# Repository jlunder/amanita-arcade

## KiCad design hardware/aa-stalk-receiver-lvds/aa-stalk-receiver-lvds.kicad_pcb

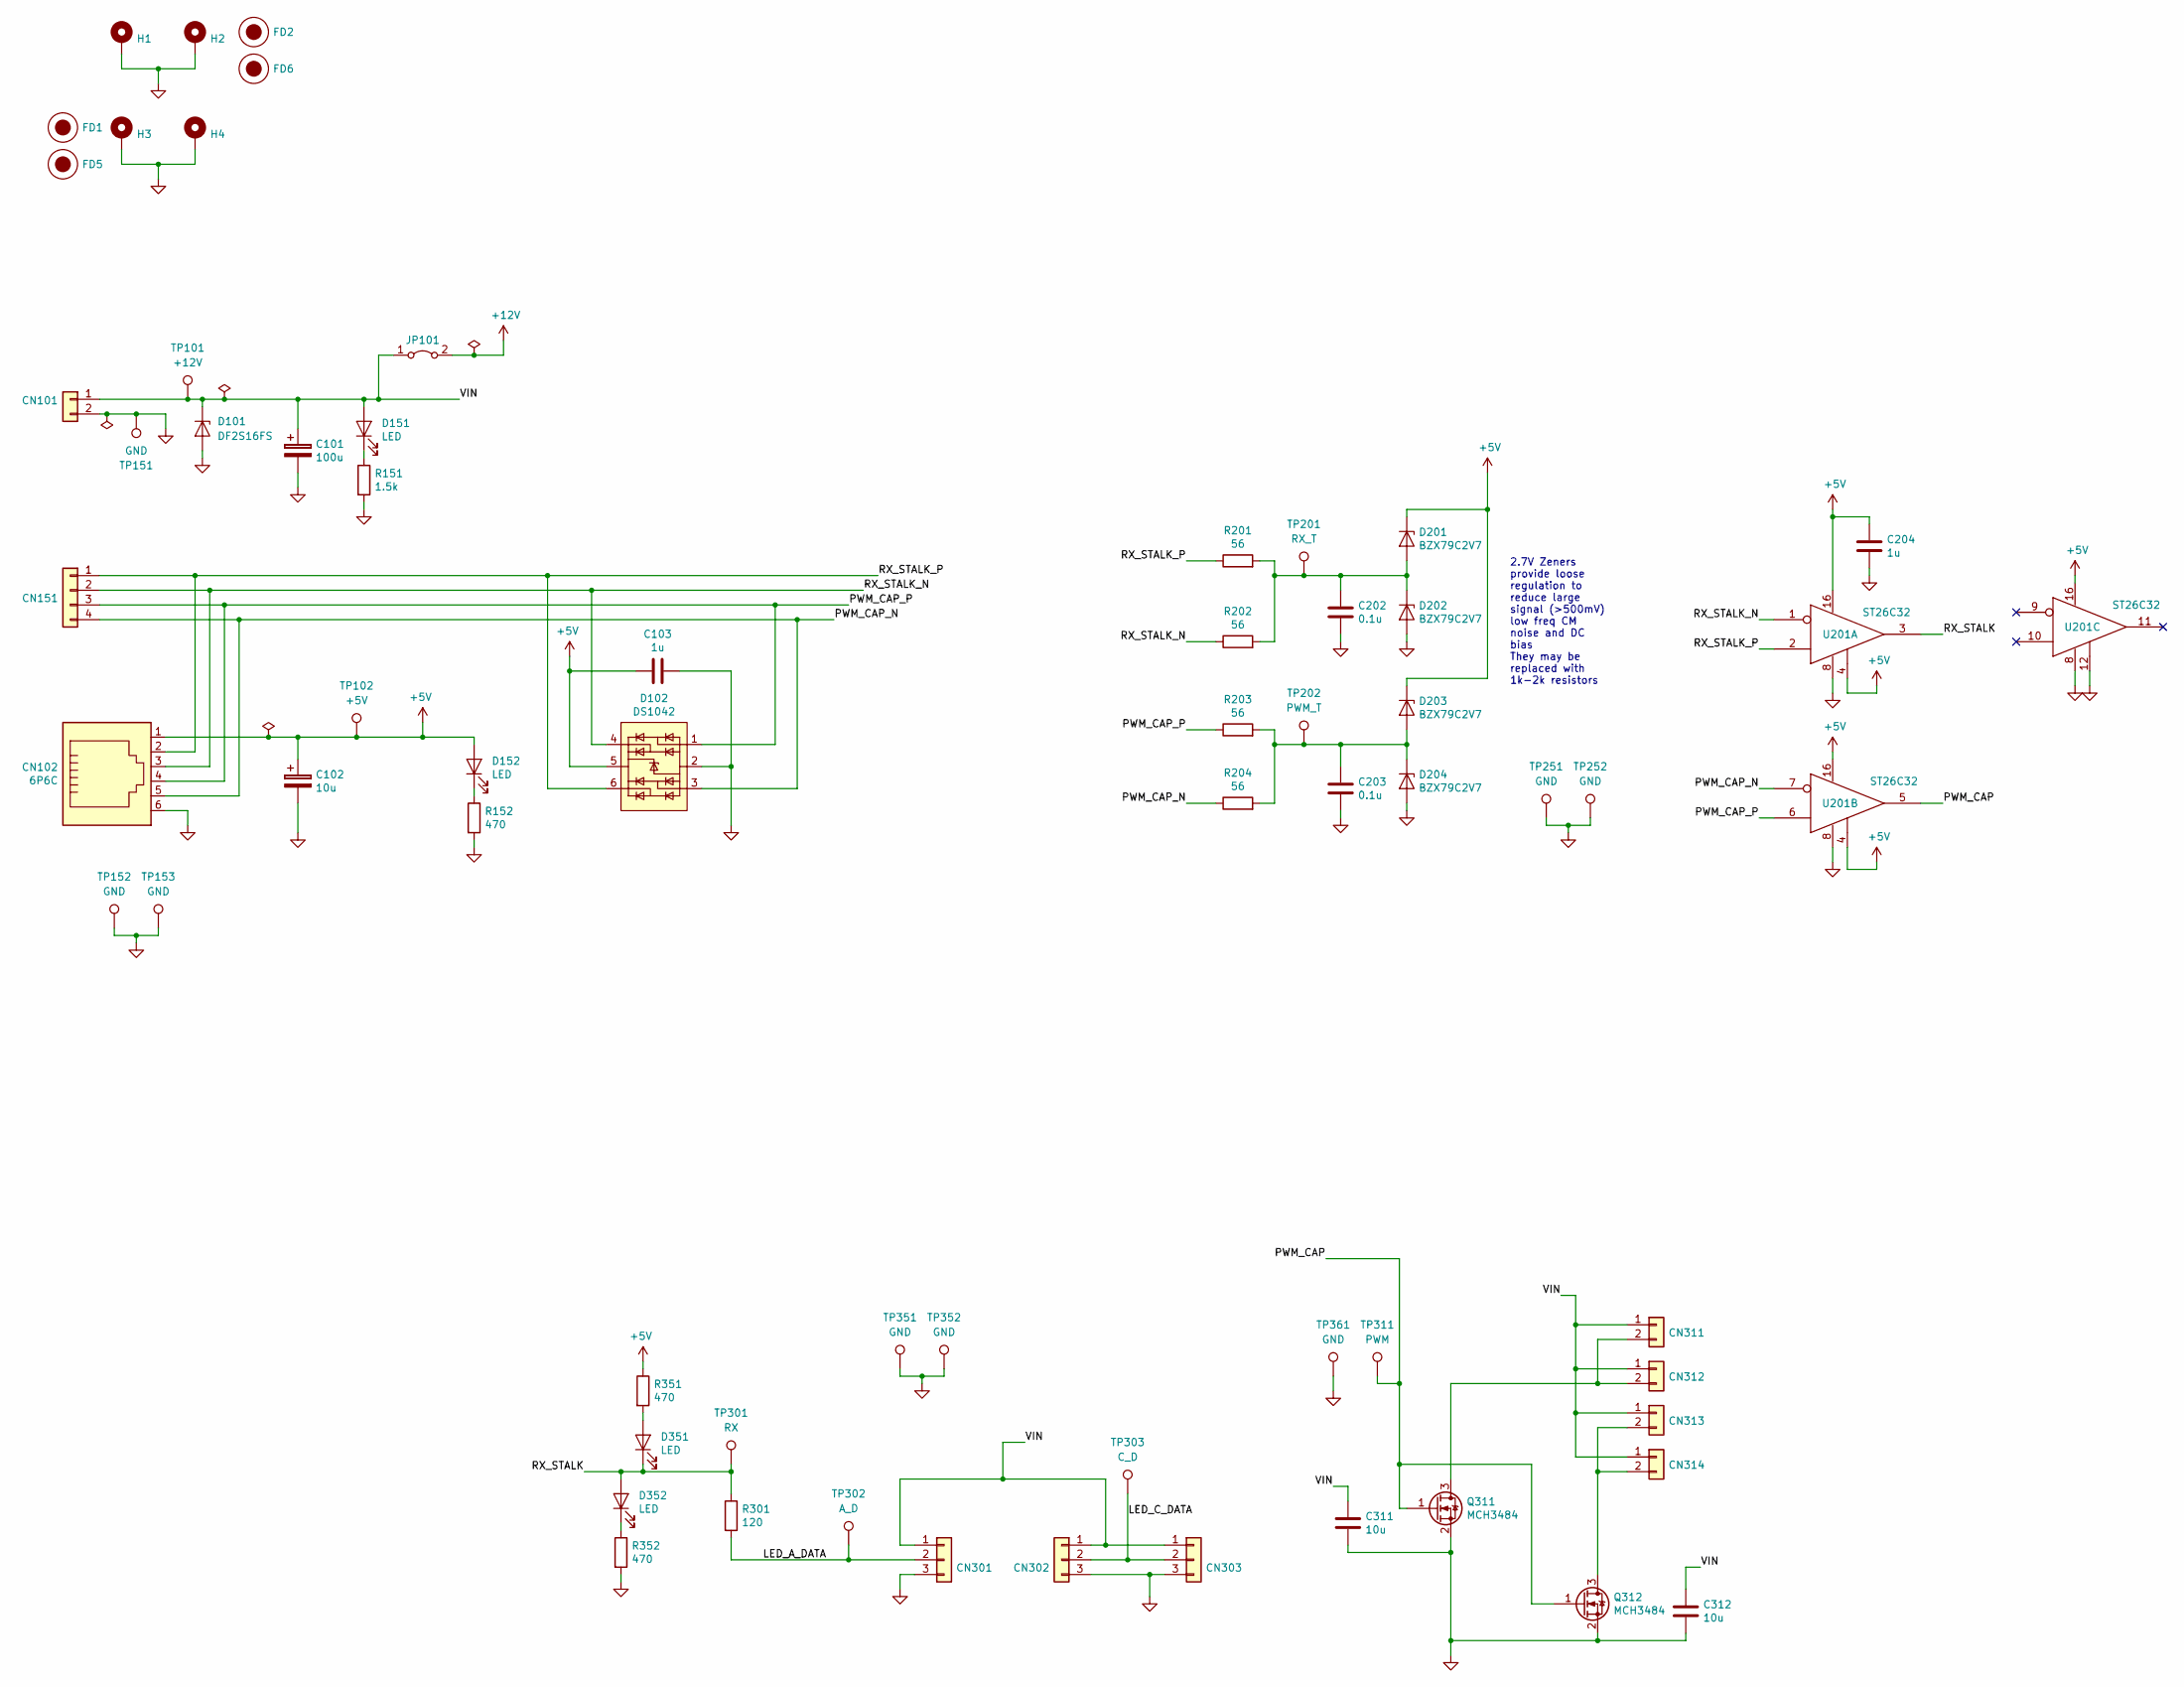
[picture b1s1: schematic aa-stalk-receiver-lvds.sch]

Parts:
C101: 100u; CP_Radial_D10.0mm_P2.50mm_P5.00mm
C102: 10u; CP_Radial_D5.0mm_P2.50mm
C103, C204: 1u; C_0805_2012Metric
C202, C203: 0.1u; C_0805_2012Metric
C311, C312: 10u; C_0805_2012Metric
CN101: Conn_01x02; SolderWirePad_1x02_P7.62mm_Drill2.5mm
CN102: 6P6C; 6P6C_Assmann_A-2014-1-4
CN151: Conn_01x04; PinHeader_1x04_P2.54mm_Vertical
CN301, CN302, CN303: Conn_01x03; PinHeader_1x03_P2.54mm_Vertical
CN311, CN312, CN313, CN314: Conn_01x02; PinHeader_1x02_P2.54mm_Vertical
D101: DF2S16FS; D_SOD-923
D102: DS1042; SOT-23-6
D151, D152, D351, D352: LED; D_0603_1608Metric
D201, D202, D203, D204: BZX79C2V7; D_DO-35_SOD27_P7.62mm_Horizontal
FD1, FD2: Fiducial; Fiducial_1mm_Dia_2.54mm_Outer_CopperTop
FD5, FD6: Fiducial; StencilAlignment_1.27mm
H1, H2, H3, H4: MountingHole_Pad; MountingHole_2.7mm_M2.5_Pad_Via
JP101: Jumper_2_Bridged; PinHeader_1x02_P2.54mm_Vertical
Q311, Q312: MCH3484; SOT-323_SC-70
R151: 1.5k; R_0603_1608Metric
R152, R351, R352: 470; R_0603_1608Metric
R201, R202, R203, R204: 56; R_0603_1608Metric
R301: 120; R_0603_1608Metric
TP101: +12V; TestPoint_Loop_D1.80mm_Drill1.0mm_Beaded
TP102: +5V; TestPoint_Loop_D1.80mm_Drill1.0mm_Beaded
TP151, TP152, TP153, TP251, TP252, TP351, TP352, TP361: GND; TestPoint_Loop_D1.80mm_Drill1.0mm_Beaded
TP201: RX_T; TestPoint_Loop_D1.80mm_Drill1.0mm_Beaded
TP202: PWM_T; TestPoint_Loop_D1.80mm_Drill1.0mm_Beaded
TP301: RX; TestPoint_Loop_D1.80mm_Drill1.0mm_Beaded
TP302: A_D; TestPoint_Loop_D1.80mm_Drill1.0mm_Beaded
TP303: C_D; TestPoint_Loop_D1.80mm_Drill1.0mm_Beaded
TP311: PWM; TestPoint_Loop_D1.80mm_Drill1.0mm_Beaded
U201: ST26C32; SOIC-16_3.9x9.9mm_P1.27mm

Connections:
+5V: C102.1, C103.2, C204.1, CN102.1, D102.5 (K), D152.2 (A), D201.1 (K), D203.1 (K), R351.1, TP102.1, U201.4 (ENABLE), U201.16 (VCC)
+12V: JP101.2 (B)
/LED_A_DATA: CN301.2, R301.2, TP302.1
/LED_C_DATA: CN302.2, CN303.2, TP303.1
/PWM_CAP: Q311.1 (G), Q312.1 (G), TP311.1, U201.5 (OUT)
/PWM_CAP_N: CN102.5, CN151.4, D102.3 (K), R204.1, U201.7 (E-)
/PWM_CAP_P: CN102.4, CN151.3, D102.1 (K), R203.1, U201.6 (E+)
/RX_STALK: D351.1 (K), D352.2 (A), R301.1, TP301.1, U201.3 (OUT)
/RX_STALK_N: CN102.3, CN151.2, D102.4 (K), R202.1, U201.1 (E-)
/RX_STALK_P: CN102.2, CN151.1, D102.6 (K), R201.1, U201.2 (E+)
/VIN: C101.1, C311.1, C312.1, CN101.1, CN301.1, CN302.1, CN303.1, CN311.1, CN312.1, CN313.1, CN314.1, D101.1 (K), D151.2 (A), JP101.1 (A), TP101.1
GND: C101.2, C102.2, C103.1, C202.2, C203.2, C204.2, C311.2, C312.2, CN101.2, CN102.6, CN301.3, CN302.3, CN303.3, D101.2 (A), D102.2 (A), D202.2 (A), D204.2 (A), H1.1, H2.1, H3.1, H4.1, Q311.2 (S), Q312.2 (S), R151.2, R152.2, R352.2, TP151.1, TP152.1, TP153.1, TP251.1, TP252.1, TP351.1, TP352.1, TP361.1, U201.8 (GND), U201.12 (ENABLE)
unnamed: C202.1, D201.2 (A), D202.1 (K), R201.2, R202.2, TP201.1
unnamed: C203.1, D203.2 (A), D204.1 (K), R203.2, R204.2, TP202.1
unnamed: CN311.2, CN312.2, Q311.3 (D)
unnamed: CN313.2, CN314.2, Q312.3 (D)
unnamed: D151.1 (K), R151.1
unnamed: D152.1 (K), R152.1
unnamed: D351.2 (A), R351.2
unnamed: D352.1 (K), R352.1

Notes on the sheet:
2.7V Zeners provide loose regulation to reduce large signal (>500mV) low freq CM noise and DC bias They may be replaced with 1k-2k resistors

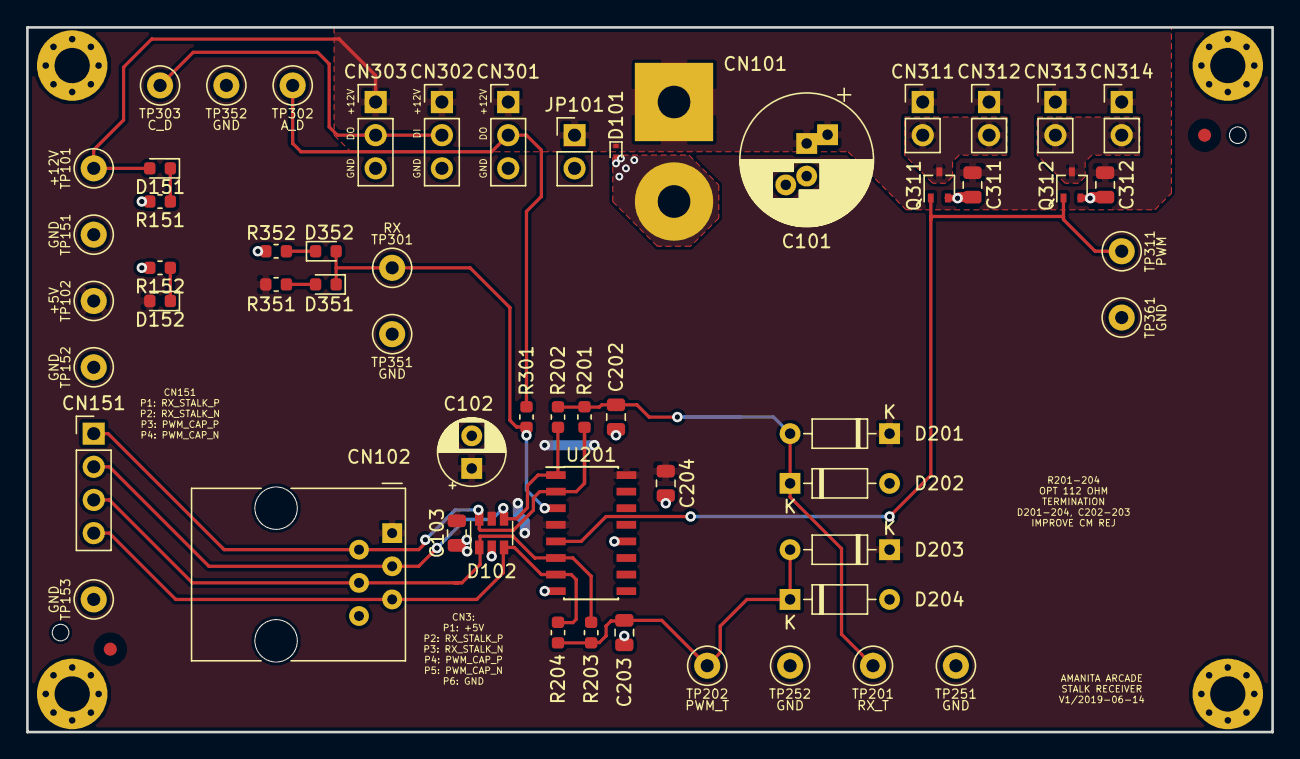
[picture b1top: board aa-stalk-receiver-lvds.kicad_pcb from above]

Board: 2 copper layers, 95.4 x 54.0 mm, 65 parts (0 on the bottom side), 19 nets.

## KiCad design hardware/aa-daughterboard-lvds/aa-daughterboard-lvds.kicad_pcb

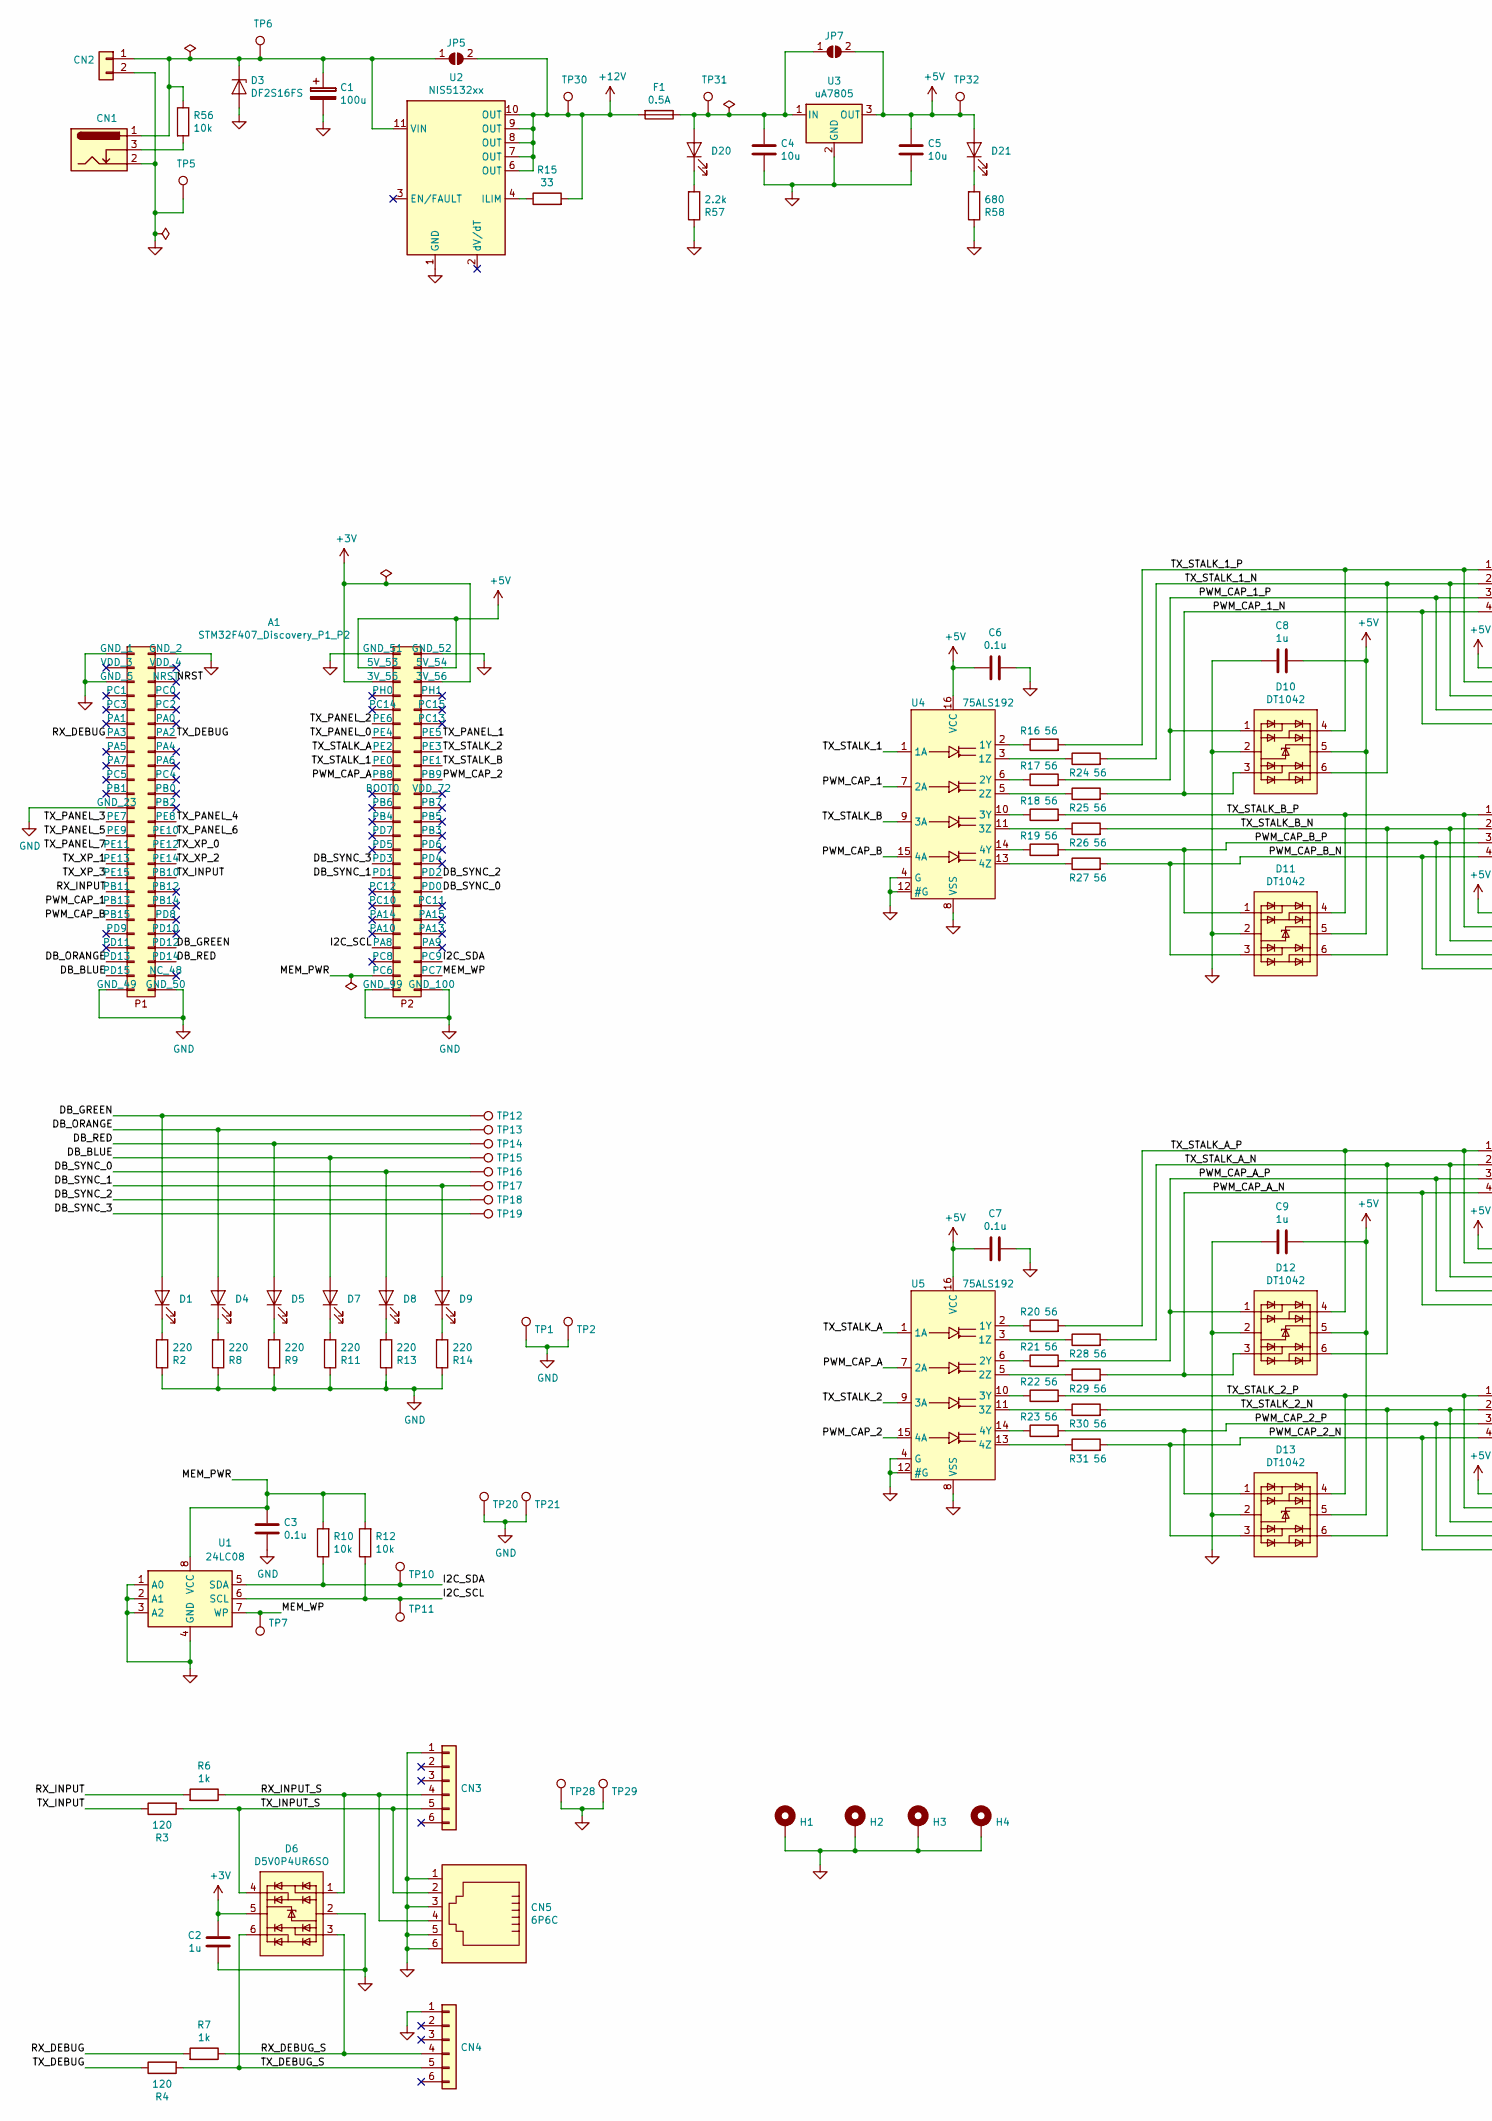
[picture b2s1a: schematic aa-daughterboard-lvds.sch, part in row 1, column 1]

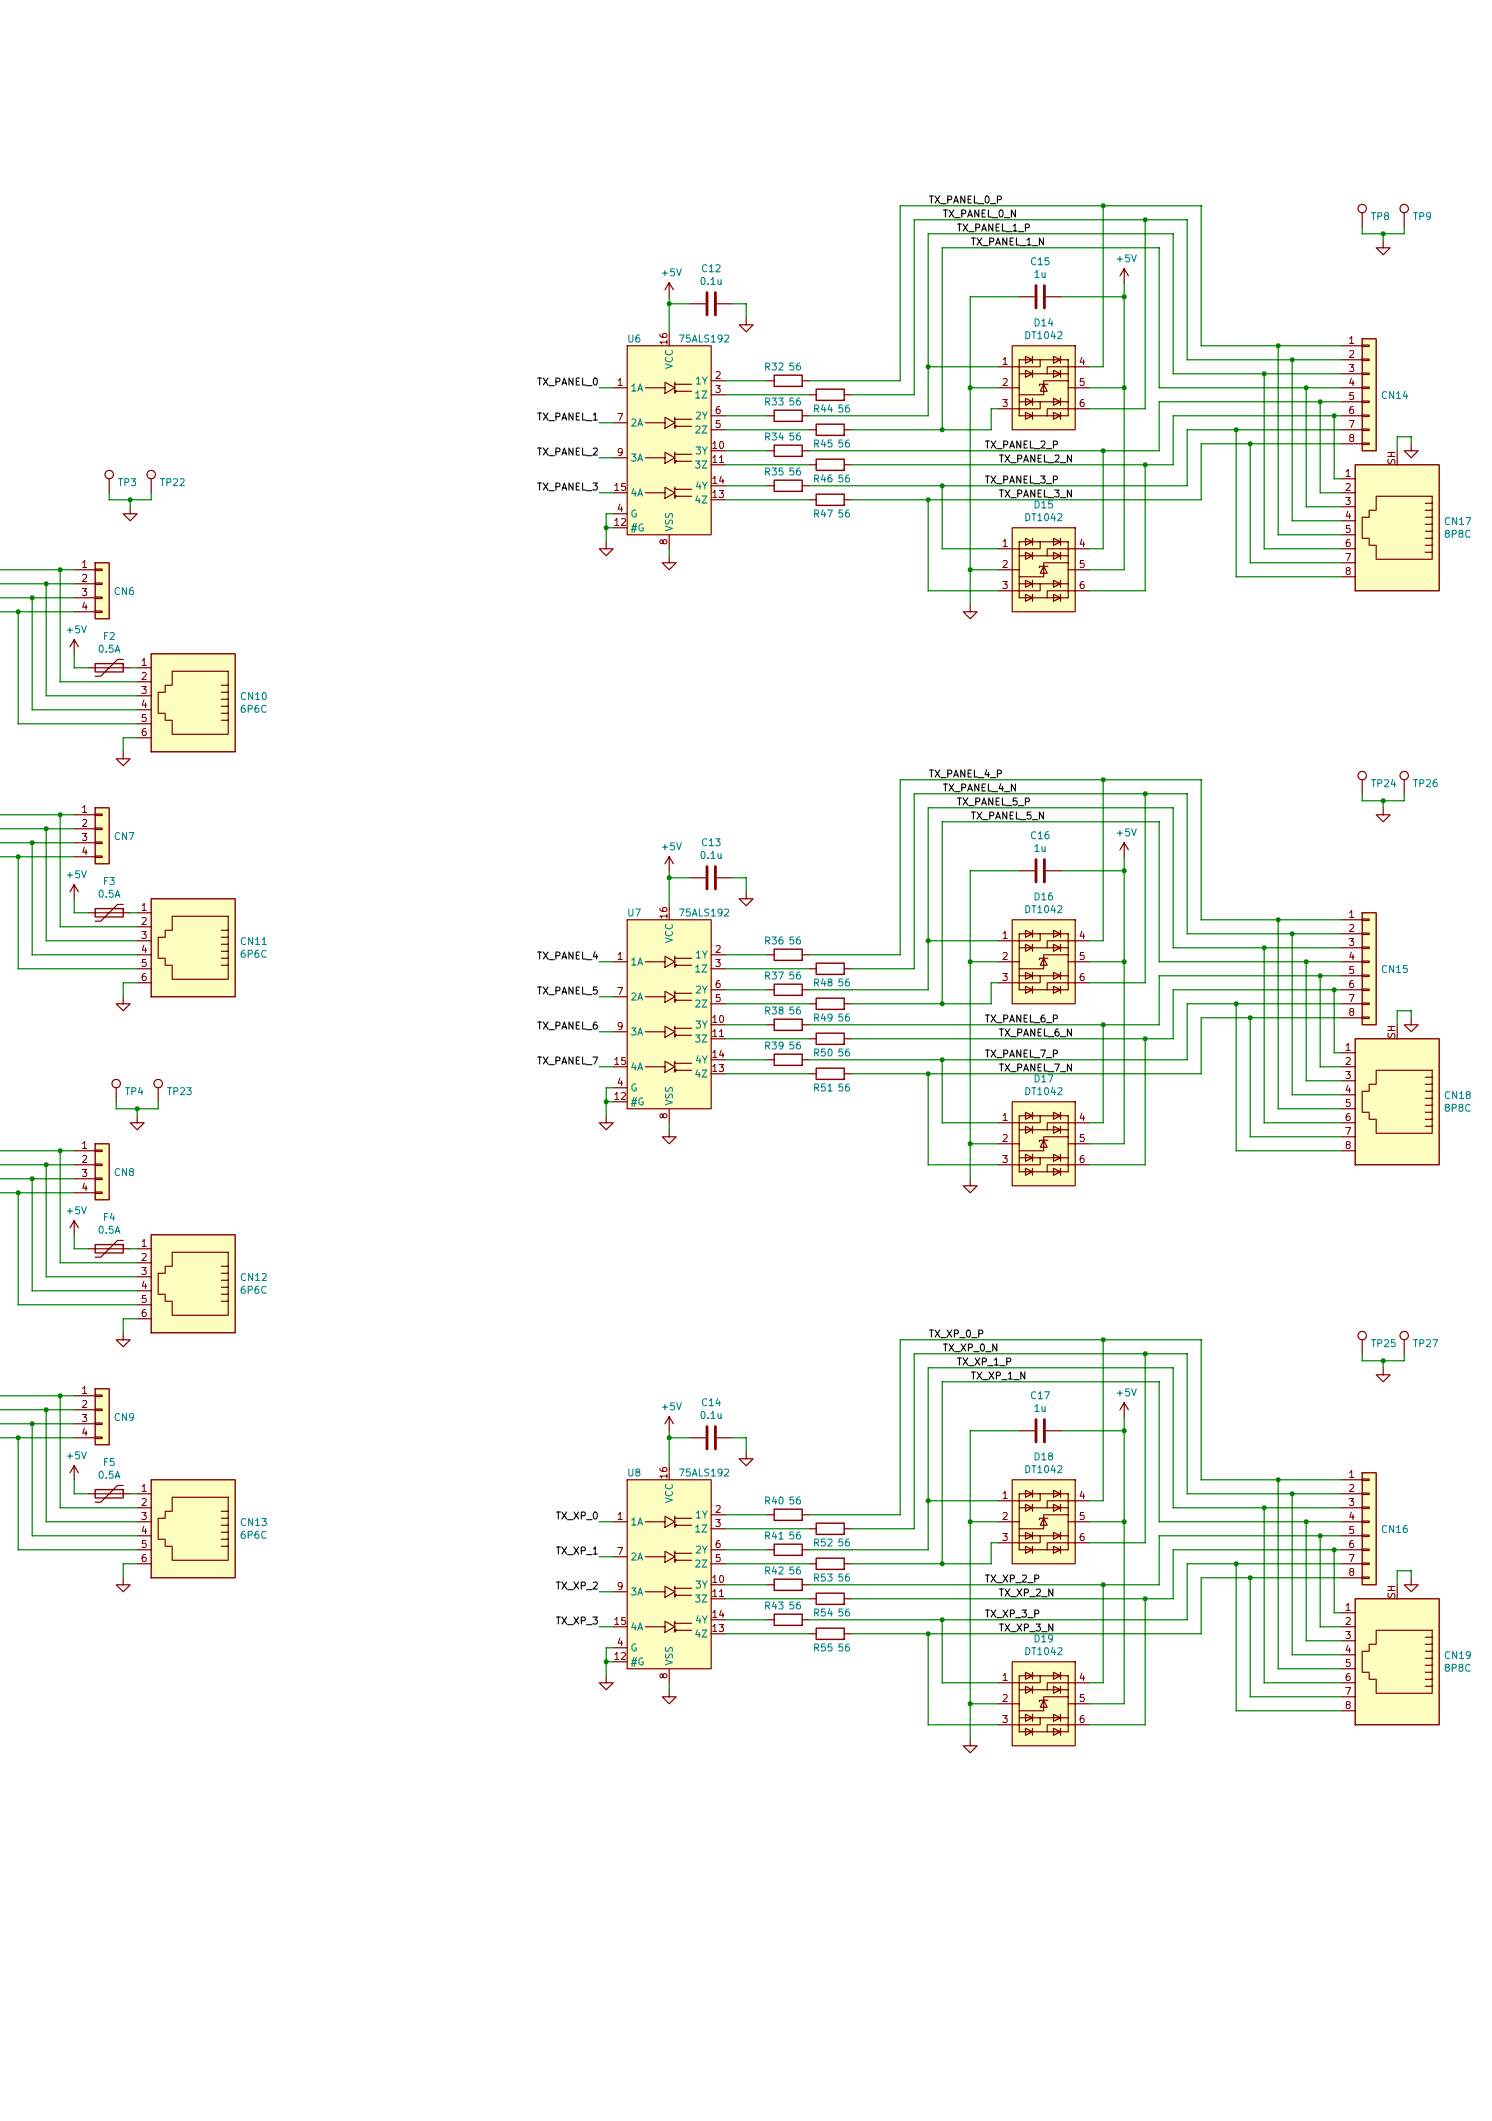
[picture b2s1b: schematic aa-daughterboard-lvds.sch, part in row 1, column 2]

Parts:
A1: STM32F407_Discovery_P1_P2; STM32F407_Discovery_P1_P2_Socket
C1: 100u; CP_Radial_D10.0mm_P2.50mm_P5.00mm
C2, C8, C9, C15, C16, C17: 1u; C_0805_2012Metric
C3, C6, C7, C12, C13, C14: 0.1u; C_0603_1608Metric
C4, C5: 10u; C_0805_2012Metric
CN1: Barrel_Jack; BarrelJack_Horizontal
CN2: Conn_01x02; SolderWirePad_1x02_P5.08mm_Drill1.5mm
CN3, CN4: Conn_01x06; PinHeader_1x06_P2.54mm_Vertical
CN5, CN10, CN11, CN12, CN13: 6P6C; 6P6C_Assmann_A-2014-1-4
CN6, CN7, CN8, CN9: Conn_01x04; PinHeader_1x04_P2.54mm_Vertical
CN14, CN15, CN16: Conn_01x08; PinHeader_2x04_P2.54mm_Vertical
CN17, CN18, CN19: 8P8C; 8P8C_Assmann_A-2014-2S-4
D1, D4, D5, D7, D8, D9, D20, D21: LED; LED_0603_1608Metric
D3: DF2S16FS; D_SOD-923
D6: D5V0P4UR6SO; SOT-23-6
D10, D11, D12, D13, D14, D15, D16, D17, D18, D19: DT1042; SOT-23-6
F1: 0.5A; Fuseholder_Clip_5x20_Bel_FC-211-22
F2, F3, F4, F5: 0.5A; Fuse_0805_2012Metric
H1, H2, H3, H4: MountingHole_Pad; MountingHole_4.3mm_M4_Pad_Via
JP5, JP7: SolderJumper_2_Open; SolderJumper-2_P1.3mm_Open_RoundedPad1.0x1.5mm
R2, R8, R9, R11, R13, R14: 220; R_0603_1608Metric
R3, R4: 120; R_0603_1608Metric
R6, R7: 1k; R_0603_1608Metric
R10, R12, R56: 10k; R_0603_1608Metric
R15: 33; R_0603_1608Metric
R16, R17, R18, R19, R20, R21, R22, R23, R24, R25, R26, R27, R28, R29, R30, R31, R32, R33, R34, R35, R36, R37, R38, R39, R40, R41, R42, R43, R44, R45, R46, R47, R48, R49, R50, R51, R52, R53, R54, R55: 56; R_0603_1608Metric
R57: 2.2k; R_0603_1608Metric
R58: 680; R_0603_1608Metric
TP1, TP2, TP3, TP4, TP5, TP6, TP7, TP8, TP9, TP10, TP11, TP12, TP13, TP14, TP15, TP16, TP17, TP18, TP19, TP20, TP21, TP22, TP23, TP24, TP25, TP26, TP27, TP28, TP29, TP30, TP31, TP32: TestPoint; TestPoint_THTPad_D2.0mm_Drill1.0mm
U1: 24LC08; DIP-8_W7.62mm_Socket
U2: NIS5132xx; DFN-10-1EP_3x3mm_P0.5mm_EP1.75x2.7mm
U3: uA7805; TO-220-3_Horizontal_TabDown
U4, U5, U6, U7, U8: 75ALS192; SOIC-16_3.9x9.9mm_P1.27mm

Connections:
+3V: A1.P2_5 (3V_55), A1.P2_6 (3V_56), C2.1, D6.5 (K)
+5V: A1.P2_3 (5V_53), A1.P2_4 (5V_54), C5.1, C6.1, C7.1, C8.2, C9.2, C12.1, C13.1, C14.1, C15.2, C16.2, C17.2, D10.5 (K), D11.5 (K), D12.5 (K), D13.5 (K), D14.5 (K), D15.5 (K), D16.5 (K), D17.5 (K), D18.5 (K), D19.5 (K), D21.2 (A), F2.2, F3.2, F4.2, F5.2, JP7.2 (B), TP32.1, U3.3 (OUT), U4.16 (VCC), U5.16 (VCC), U6.16 (VCC), U7.16 (VCC), U8.16 (VCC); also elsewhere on the board
+12V: F1.2, JP5.2 (B), R15.2, TP30.1, U2.6 (OUT), U2.7 (OUT), U2.8 (OUT), U2.9 (OUT), U2.10 (OUT)
/DB_BLUE: A1.P1_47 (PD15), D7.2 (A), TP15.1
/DB_GREEN: A1.P1_44 (PD12), D1.2 (A), TP12.1
/DB_ORANGE: A1.P1_45 (PD13), D4.2 (A), TP13.1
/DB_RED: A1.P1_46 (PD14), D5.2 (A), TP14.1
/DB_SYNC_0: A1.P2_36 (PD0), D8.2 (A), TP16.1
/DB_SYNC_1: A1.P2_33 (PD1), D9.2 (A), TP17.1
/DB_SYNC_2: A1.P2_34 (PD2), TP18.1
/DB_SYNC_3: A1.P2_31 (PD3), TP19.1
/I2C_SCL: A1.P2_43 (PA8), R12.1, TP11.1, U1.6 (SCL)
/I2C_SDA: A1.P2_46 (PC9), R10.1, TP10.1, U1.5 (SDA)
/MEM_PWR: A1.P2_47 (PC6), C3.1, R10.2, R12.2, U1.8 (VCC)
/MEM_WP: A1.P2_48 (PC7), TP7.1, U1.7 (WP)
/NRST: A1.P1_6 (NRST)
/PWM_CAP_1: A1.P1_37 (PB13), U4.7 (2A)
/PWM_CAP_1_N: CN6.4, CN10.5, D10.3 (K), R25.2
/PWM_CAP_1_P: CN6.3, CN10.4, D10.1 (K), R17.2
/PWM_CAP_2: A1.P2_20 (PB9), U5.15 (4A)
/PWM_CAP_2_N: CN9.4, CN13.5, D13.3 (K), R31.2
/PWM_CAP_2_P: CN9.3, CN13.4, D13.1 (K), R23.2
/PWM_CAP_A: A1.P2_19 (PB8), U5.7 (2A)
/PWM_CAP_A_N: CN8.4, CN12.5, D12.3 (K), R29.2
/PWM_CAP_A_P: CN8.3, CN12.4, D12.1 (K), R21.2
/PWM_CAP_B: A1.P1_39 (PB15), U4.15 (4A)
/PWM_CAP_B_N: CN7.4, CN11.5, D11.3 (K), R27.2
/PWM_CAP_B_P: CN7.3, CN11.4, D11.1 (K), R19.2
/RX_DEBUG: A1.P1_13 (PA3), R7.2
/RX_DEBUG_S: CN4.4, D6.3 (K), R7.1
/RX_INPUT: A1.P1_35 (PB11), R6.2
/RX_INPUT_S: CN3.4, CN5.4, D6.1 (K), R6.1
/TX_DEBUG: A1.P1_14 (PA2), R4.1
/TX_DEBUG_S: CN4.5, D6.6 (K), R4.2
/TX_INPUT: A1.P1_34 (PB10), R3.1
/TX_INPUT_S: CN3.5, CN5.2, D6.4 (K), R3.2
/TX_PANEL_0: A1.P2_13 (PE4), U6.1 (1A)
/TX_PANEL_0_N: CN14.2, CN17.4, D14.6 (K), R44.2
/TX_PANEL_0_P: CN14.1, CN17.5, D14.4 (K), R32.2
/TX_PANEL_1: A1.P2_14 (PE5), U6.7 (2A)
/TX_PANEL_1_N: CN14.4, CN17.3, D14.3 (K), R45.2
/TX_PANEL_1_P: CN14.3, CN17.6, D14.1 (K), R33.2
/TX_PANEL_2: A1.P2_11 (PE6), U6.9 (3A)
/TX_PANEL_2_N: CN14.6, CN17.1, D15.6 (K), R46.2
/TX_PANEL_2_P: CN14.5, CN17.2, D15.4 (K), R34.2
/TX_PANEL_3: A1.P1_25 (PE7), U6.15 (4A)
/TX_PANEL_3_N: CN14.8, CN17.7, D15.3 (K), R47.2
/TX_PANEL_3_P: CN14.7, CN17.8, D15.1 (K), R35.2
/TX_PANEL_4: A1.P1_26 (PE8), U7.1 (1A)
/TX_PANEL_4_N: CN15.2, CN18.4, D16.6 (K), R48.2
/TX_PANEL_4_P: CN15.1, CN18.5, D16.4 (K), R36.2
/TX_PANEL_5: A1.P1_27 (PE9), U7.7 (2A)
/TX_PANEL_5_N: CN15.4, CN18.3, D16.3 (K), R49.2
/TX_PANEL_5_P: CN15.3, CN18.6, D16.1 (K), R37.2
/TX_PANEL_6: A1.P1_28 (PE10), U7.9 (3A)
/TX_PANEL_6_N: CN15.6, CN18.1, D17.6 (K), R50.2
/TX_PANEL_6_P: CN15.5, CN18.2, D17.4 (K), R38.2
/TX_PANEL_7: A1.P1_29 (PE11), U7.15 (4A)
/TX_PANEL_7_N: CN15.8, CN18.7, D17.3 (K), R51.2
/TX_PANEL_7_P: CN15.7, CN18.8, D17.1 (K), R39.2
/TX_STALK_1: A1.P2_17 (PE0), U4.1 (1A)
/TX_STALK_1_N: CN6.2, CN10.3, D10.6 (K), R24.2
/TX_STALK_1_P: CN6.1, CN10.2, D10.4 (K), R16.2
/TX_STALK_2: A1.P2_16 (PE3), U5.9 (3A)
/TX_STALK_2_N: CN9.2, CN13.3, D13.6 (K), R30.2
/TX_STALK_2_P: CN9.1, CN13.2, D13.4 (K), R22.2
/TX_STALK_A: A1.P2_15 (PE2), U5.1 (1A)
/TX_STALK_A_N: CN8.2, CN12.3, D12.6 (K), R28.2
/TX_STALK_A_P: CN8.1, CN12.2, D12.4 (K), R20.2
/TX_STALK_B: A1.P2_18 (PE1), U4.9 (3A)
/TX_STALK_B_N: CN7.2, CN11.3, D11.6 (K), R26.2
/TX_STALK_B_P: CN7.1, CN11.2, D11.4 (K), R18.2
/TX_XP_0: A1.P1_30 (PE12), U8.1 (1A)
/TX_XP_0_N: CN16.2, CN19.4, D18.6 (K), R52.2
/TX_XP_0_P: CN16.1, CN19.5, D18.4 (K), R40.2
/TX_XP_1: A1.P1_31 (PE13), U8.7 (2A)
/TX_XP_1_N: CN16.4, CN19.3, D18.3 (K), R53.2
/TX_XP_1_P: CN16.3, CN19.6, D18.1 (K), R41.2
/TX_XP_2: A1.P1_32 (PE14), U8.9 (3A)
/TX_XP_2_N: CN16.6, CN19.1, D19.6 (K), R54.2
/TX_XP_2_P: CN16.5, CN19.2, D19.4 (K), R42.2
/TX_XP_3: A1.P1_33 (PE15), U8.15 (4A)
/TX_XP_3_N: CN16.8, CN19.7, D19.3 (K), R55.2
/TX_XP_3_P: CN16.7, CN19.8, D19.1 (K), R43.2
GND: A1.P1_1 (GND_1), A1.P1_2 (GND_2), A1.P1_5 (GND_5), A1.P1_23 (GND_23), A1.P1_49 (GND_49), A1.P1_50 (GND_50), A1.P2_1 (GND_51), A1.P2_2 (GND_52), A1.P2_49 (GND_99), A1.P2_50 (GND_100), C1.2, C2.2, C3.2, C4.2, C5.2, C6.2, C7.2, C8.1, C9.1, C12.2, C13.2, C14.2, C15.1, C16.1, C17.1, CN1.2, CN2.2, CN3.1, CN4.1, CN5.1, CN5.3, CN5.5, CN5.6, CN10.6, CN11.6, CN12.6, CN13.6, CN17.SH, CN18.SH, CN19.SH, D3.2 (A), D6.2 (A), D10.2 (A), D11.2 (A), D12.2 (A), D13.2 (A), D14.2 (A), D15.2 (A), D16.2 (A), D17.2 (A), D18.2 (A), D19.2 (A), H1.1, H2.1, H3.1, H4.1, R2.1, R8.1, R9.1, R11.1, R13.1, R14.1, R57.1, R58.1, TP1.1, TP2.1, TP3.1, TP4.1, TP5.1, TP8.1, TP9.1, TP20.1, TP21.1, TP22.1, TP23.1, TP24.1, TP25.1, TP26.1, TP27.1, TP28.1, TP29.1, U1.1 (A0), U1.2 (A1), U1.3 (A2), U1.4 (GND), U2.1 (GND), U3.2 (GND), U4.4 (G), U4.8 (VSS), U4.12 (#G), U5.4 (G), U5.8 (VSS), U5.12 (#G), U6.4 (G), U6.8 (VSS), U6.12 (#G), U7.4 (G), U7.8 (VSS), U7.12 (#G), U8.4 (G), U8.8 (VSS), U8.12 (#G); also elsewhere on the board
unnamed: C1.1, CN1.1, CN2.1, D3.1 (K), JP5.1 (A), R56.1, TP6.1, U2.11 (VIN)
unnamed 135: C4.1, D20.2 (A), F1.1, JP7.1 (A), TP31.1, U3.1 (IN); also elsewhere on the board
unnamed: CN1.3, R56.2
unnamed: CN10.1, F2.1
unnamed: CN11.1, F3.1
unnamed: CN12.1, F4.1
unnamed: CN13.1, F5.1
unnamed: D1.1 (K), R2.2
unnamed: D4.1 (K), R8.2
unnamed: D5.1 (K), R9.2
unnamed: D7.1 (K), R11.2
unnamed: D8.1 (K), R13.2
unnamed: D9.1 (K), R14.2
unnamed: D20.1 (K), R57.2
unnamed: D21.1 (K), R58.2
unnamed: R15.1, U2.4 (ILIM)
unnamed: R16.1, U4.2 (1Y)
unnamed: R17.1, U4.6 (2Y)
unnamed: R18.1, U4.10 (3Y)
unnamed: R19.1, U4.14 (4Y)
unnamed: R20.1, U5.2 (1Y)
unnamed: R21.1, U5.6 (2Y)
unnamed: R22.1, U5.10 (3Y)
unnamed: R23.1, U5.14 (4Y)
unnamed: R24.1, U4.3 (1Z)
unnamed: R25.1, U4.5 (2Z)
unnamed: R26.1, U4.11 (3Z)
unnamed: R27.1, U4.13 (4Z)
unnamed: R28.1, U5.3 (1Z)
unnamed: R29.1, U5.5 (2Z)
unnamed: R30.1, U5.11 (3Z)
unnamed: R31.1, U5.13 (4Z)
unnamed: R32.1, U6.2 (1Y)
unnamed: R33.1, U6.6 (2Y)
unnamed: R34.1, U6.10 (3Y)
unnamed: R35.1, U6.14 (4Y)
unnamed: R36.1, U7.2 (1Y)
unnamed: R37.1, U7.6 (2Y)
unnamed: R38.1, U7.10 (3Y)
unnamed: R39.1, U7.14 (4Y)
unnamed: R40.1, U8.2 (1Y)
unnamed: R41.1, U8.6 (2Y)
unnamed: R42.1, U8.10 (3Y)
unnamed: R43.1, U8.14 (4Y)
unnamed: R44.1, U6.3 (1Z)
unnamed: R45.1, U6.5 (2Z)
unnamed: R46.1, U6.11 (3Z)
unnamed: R47.1, U6.13 (4Z)
unnamed: R48.1, U7.3 (1Z)
unnamed: R49.1, U7.5 (2Z)
unnamed: R50.1, U7.11 (3Z)
unnamed: R51.1, U7.13 (4Z)
unnamed: R52.1, U8.3 (1Z)
unnamed: R53.1, U8.5 (2Z)
unnamed: R54.1, U8.11 (3Z)
unnamed: R55.1, U8.13 (4Z)

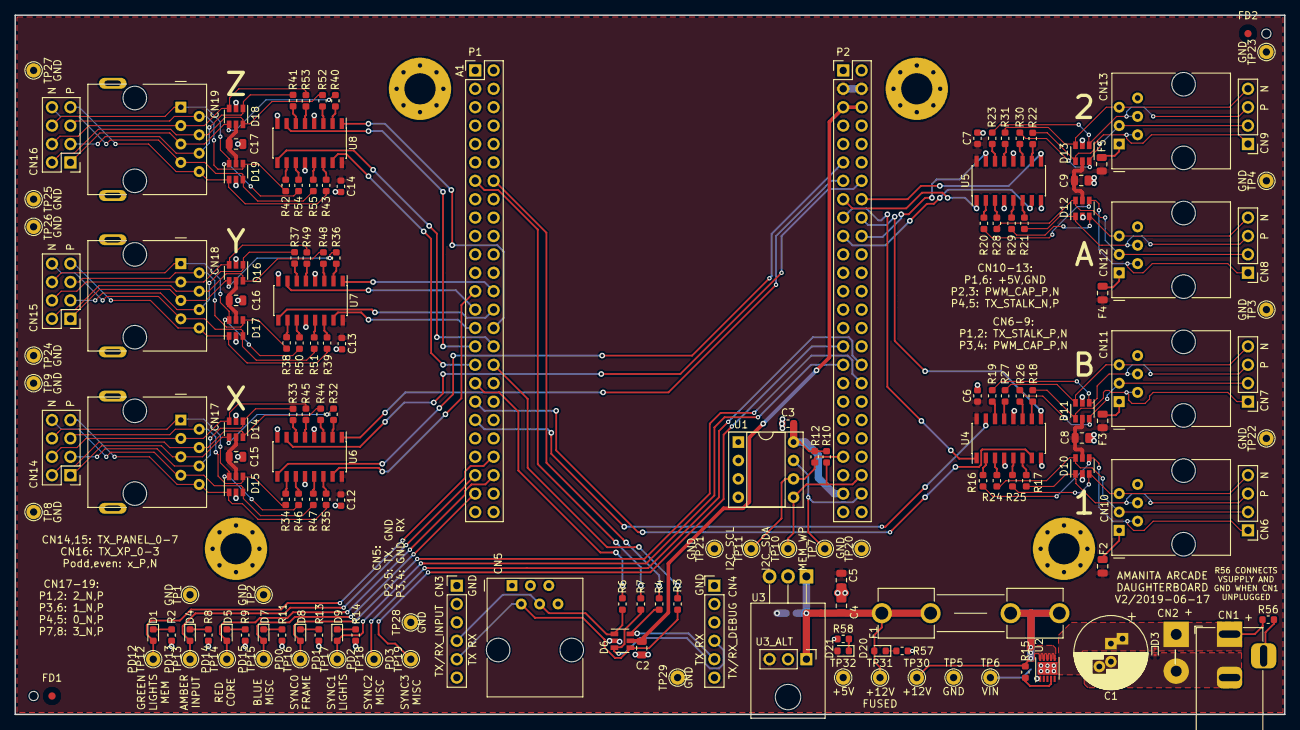
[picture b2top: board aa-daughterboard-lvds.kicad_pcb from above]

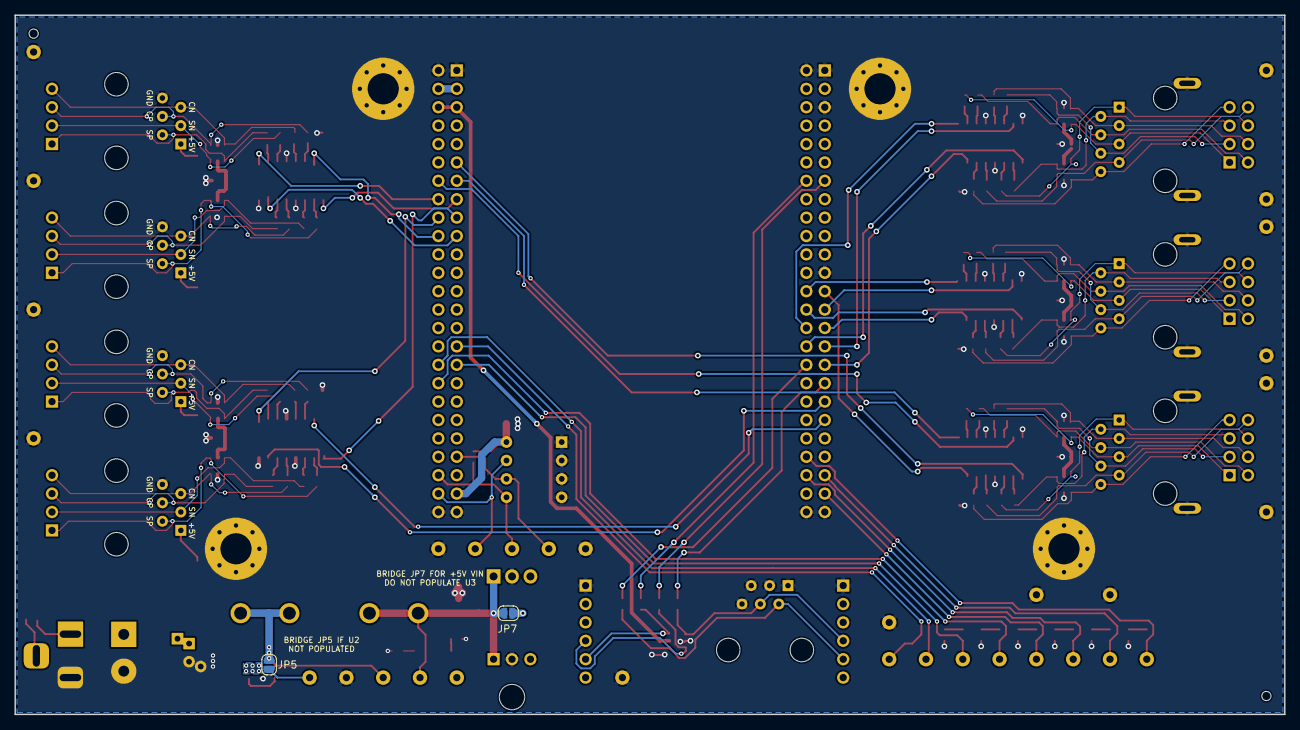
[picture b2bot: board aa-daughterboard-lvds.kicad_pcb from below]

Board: 4 copper layers, 175.3 x 96.5 mm, 167 parts (2 on the bottom side), 140 nets.

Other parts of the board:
FD1, FD2: Fiducial_1mm_Dia_2.54mm_Outer_CopperTop
FD5, FD6: StencilAlignment_1.27mm
U3_ALT: PinHeader_1x03_P2.54mm_Vertical

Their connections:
+5V: U3_ALT.3; also elsewhere on the board
GND: U3_ALT.2; also elsewhere on the board
unnamed 135: U3_ALT.1; also elsewhere on the board
